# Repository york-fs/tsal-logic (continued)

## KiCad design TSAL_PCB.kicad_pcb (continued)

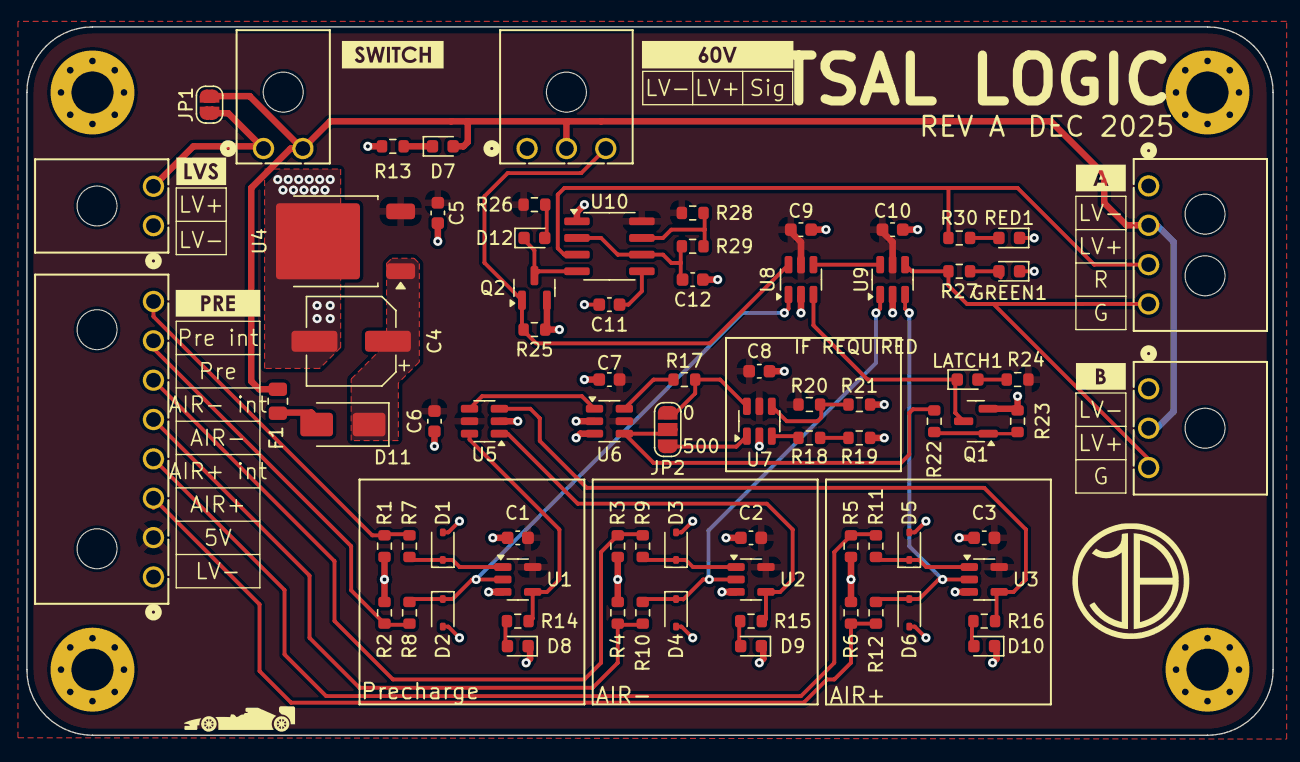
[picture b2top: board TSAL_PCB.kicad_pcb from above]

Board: 2 copper layers, 95.0 x 54.0 mm, 84 parts (0 on the bottom side), 47 nets.

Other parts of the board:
kibuzzard-69304CEA: G***; kibuzzard-69304CEA
kibuzzard-69304CF6: G***; kibuzzard-69304CF6
kibuzzard-69304CFD: G***; kibuzzard-69304CFD
kibuzzard-69304D07: G***; kibuzzard-69304D07
kibuzzard-69304E4B: G***; kibuzzard-69304E4B
kibuzzard-693052B2: G***; kibuzzard-693052B2
